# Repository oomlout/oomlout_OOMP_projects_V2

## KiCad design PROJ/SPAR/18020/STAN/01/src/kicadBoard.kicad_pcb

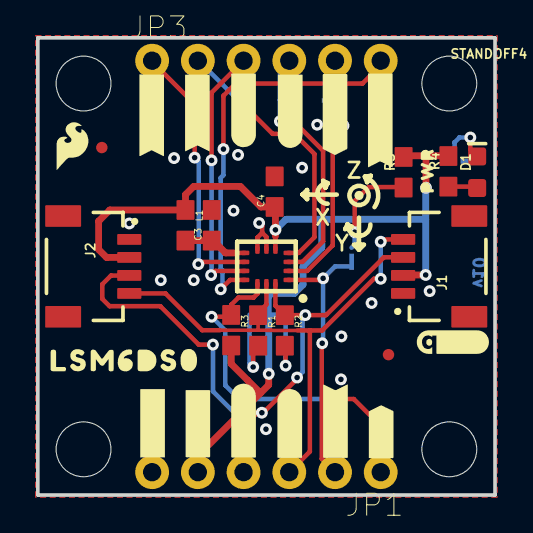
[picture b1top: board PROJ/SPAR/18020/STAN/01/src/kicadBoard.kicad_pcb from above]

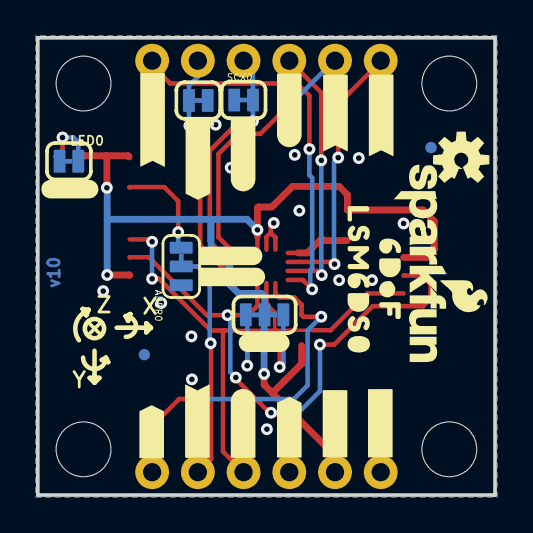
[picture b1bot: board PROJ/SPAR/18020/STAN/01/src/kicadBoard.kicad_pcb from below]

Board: 2 copper layers, 25.4 x 25.4 mm, 64 parts (27 on the bottom side), 18 nets.

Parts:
ADDR0: JUMPER-SMT_3_1-NC_TRACE_SILK; SMT-JUMPER_3_1-NC_TRACE_SILK
C3, C4: 0.1uF; 0603
D1: RED; LED-0603
FD1, FD2: FIDUCIALUFIDUCIAL; FIDUCIAL-MICRO
FID1, FID2: FIDUCIALUFIDUCIAL; FIDUCIAL-MICRO
FRAME1: FRAME-LETTER; CREATIVE_COMMONS
I2C_PU0: S_MODE; SMT-JUMPER_3_2-NC_TRACE_SILK
J1, J2: QWIIC_RIGHT_ANGLE; JST04_1MM_RA
JP1, JP3: IO; 1X06_NO_SILK
L1: 30Ω; 0603
LED0: JUMPER-SMT_2_NC_TRACE_SILK; SMT-JUMPER_2_NC_TRACE_SILK
LOGO1: QWIIC_LOGO_4MM; QWIIC_4MM
LOGO2: OSHW-LOGOS; OSHW-LOGO-S
LOGO3: SFE_LOGO_NAME_FLAME.1_INCH; SFE_LOGO_NAME_FLAME_.1
R1, R2: 4.7k; 0603
R3: 10k; 0603
R4: 1k; 0603
R5: 100k; 0603
SCX0: JUMPER-SMT_2_NC_TRACE_SILK; SMT-JUMPER_2_NC_TRACE_SILK
SDX0: JUMPER-SMT_2_NC_TRACE_SILK; SMT-JUMPER_2_NC_TRACE_SILK
STANDOFF1, STANDOFF2, STANDOFF3, STANDOFF4: STAND-OFFTIGHT; STAND-OFF-TIGHT
U1: LSM6DS0; LGA14L
U$1, U$15: #3V3#1
U$2, U$17: #GND#0
U$3: ##CS##7
U$4: #SDA#4
U$5, U$22: #SCL#5
U$6: #SDO#6
U$7, U$19: #INT1#9
U$8, U$21: #INT2#9
U$9: #OCS#8
U$10: #SCX#9
U$11, U$33: #SDIX#11
U$12, U$30: LSM6DS011
U$13: #0X6A#11
U$14: #0X6B#11
U$16: #LED#11
U$18: #SDO#7
U$20: #OCS#7
U$23: #SCX#8
U$24, U$32: #SDOX#12
U$25: #I2C#11
U$26: #SDI#4
U$27: ##CS##8
U$28: PWR8
U$29: SFE_LOGO_FLAME_.1
U$31: 6DOF12

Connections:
3.3V: C4.1, I2C_PU0.2, J1.2, J2.2, JP1.5, L1.1, R3.2, R4.2, R5.2, U1.5
GND: ADDR0.1, C3.2, C4.2, J1.1, J2.1, JP1.6, LED0.1, SCX0.1, SDX0.1, U1.6, U1.7
INT1: JP3.2, U1.4
INT2: JP3.1, U1.9
unnamed: ADDR0.3, R5.1
unnamed: D1.A, R4.1
unnamed: D1.C, LED0.2
unnamed: I2C_PU0.1, R1.2
unnamed: I2C_PU0.3, R2.2
OCS: JP3.3, U1.10
SCL: J1.4, J2.4, JP1.3, R1.1, U1.13
SCX: JP3.4, SCX0.2, U1.3
SDA: J1.3, J2.3, JP1.4, R2.1, U1.14
SDI_AUX: JP3.5, SDX0.2, U1.2
SDO/SA0: ADDR0.2, JP1.2, U1.1
SDO_AUX: JP3.6, U1.11
VDD: C3.1, L1.2, U1.8
~CS: JP1.1, R3.1, U1.12

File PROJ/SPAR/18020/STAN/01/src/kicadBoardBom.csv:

"Id";"Designator";"Package";"Quantity";"Designation";"Supplier and ref";
1;"U$30,U$12";"LSM6DS011";2;"";;;
2;"C3,C4";"0603";2;"0.1uF";;;
3;"STANDOFF4,STANDOFF3,STANDOFF2,STANDOFF1";"STAND-OFF-TIGHT";4;"STAND-OFFTIGHT";;;
4;"J1,J2";"JST04_1MM_RA";2;"QWIIC_RIGHT_ANGLE";;;
5;"L1";"0603";1;"30Ω";;;
6;"FID1,FID2,FD2,FD1";"FIDUCIAL-MICRO";4;"FIDUCIALUFIDUCIAL";;;
7;"LOGO1";"QWIIC_4MM";1;"QWIIC_LOGO_4MM";;;
8;"U$28";"PWR8";1;"";;;
9;"U$6";"#SDO#6";1;"";;;
10;"R3";"0603";1;"10k";;;
11;"U$2,U$17";"#GND#0";2;"";;;
12;"R1,R2";"0603";2;"4.7k";;;
13;"JP1,JP3";"1X06_NO_SILK";2;"IO";;;
14;"U$3";"##CS##7";1;"";;;
15;"R4";"0603";1;"1k";;;
16;"U$4";"#SDA#4";1;"";;;
17;"R5";"0603";1;"100k";;;
18;"U$8,U$21";"#INT2#9";2;"";;;
19;"FRAME1";"CREATIVE_COMMONS";1;"FRAME-LETTER";;;
20;"U$1,U$15";"#3V3#1";2;"";;;
21;"U$5,U$22";"#SCL#5";2;"";;;
22;"U$11,U$33";"#SDIX#11";2;"";;;
23;"U$24,U$32";"#SDOX#12";2;"";;;
24;"U$10";"#SCX#9";1;"";;;
25;"U$9";"#OCS#8";1;"";;;
26;"U$7,U$19";"#INT1#9";2;"";;;
27;"U1";"LGA14L";1;"LSM6DS0";;;
28;"U$29";"SFE_LOGO_FLAME_.1";1;"";;;
29;"D1";"LED-0603";1;"RED";;;
30;"U$31";"6DOF12";1;"";;;
31;"U$14";"#0X6B#11";1;"";;;
32;"ADDR0";"SMT-JUMPER_3_1-NC_TRACE_SILK";1;"JUMPER-SMT_3_1-NC_TRACE_SILK";;;
33;"I2C_PU0";"SMT-JUMPER_3_2-NC_TRACE_SILK";1;"S_MODE";;;
34;"U$25";"#I2C#11";1;"";;;
35;"LOGO3";"SFE_LOGO_NAME_FLAME_.1";1;"SFE_LOGO_NAME_FLAME.1_INCH";;;
36;"U$16";"#LED#11";1;"";;;
37;"SCX0,SDX0,LED0";"SMT-JUMPER_2_NC_TRACE_SILK";3;"JUMPER-SMT_2_NC_TRACE_SILK";;;
38;"U$18";"#SDO#7";1;"";;;
39;"U$26";"#SDI#4";1;"";;;
40;"LOGO2";"OSHW-LOGO-S";1;"OSHW-LOGOS";;;
41;"U$23";"#SCX#8";1;"";;;
42;"U$13";"#0X6A#11";1;"";;;
43;"U$20";"#OCS#7";1;"";;;
44;"U$27";"##CS##8";1;"";;;

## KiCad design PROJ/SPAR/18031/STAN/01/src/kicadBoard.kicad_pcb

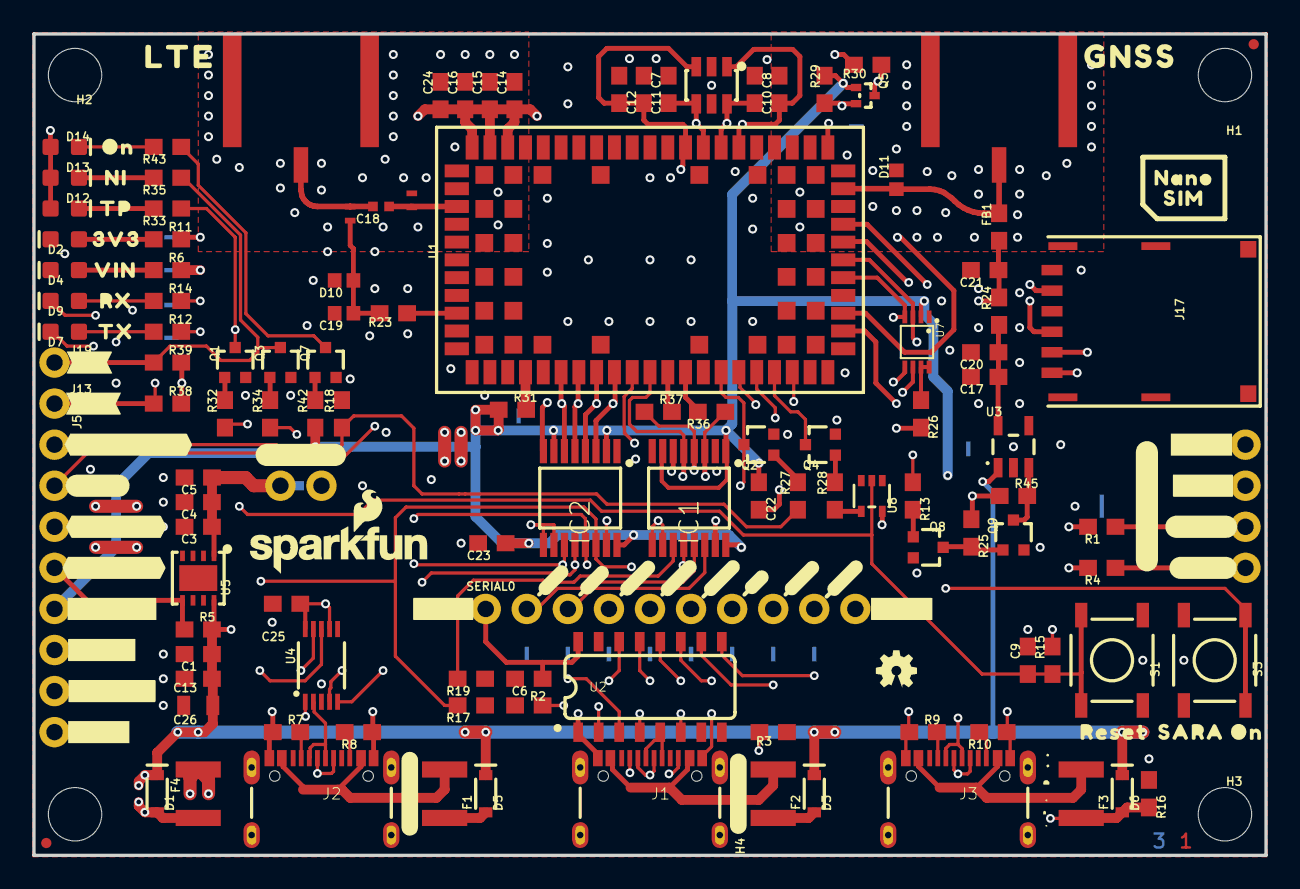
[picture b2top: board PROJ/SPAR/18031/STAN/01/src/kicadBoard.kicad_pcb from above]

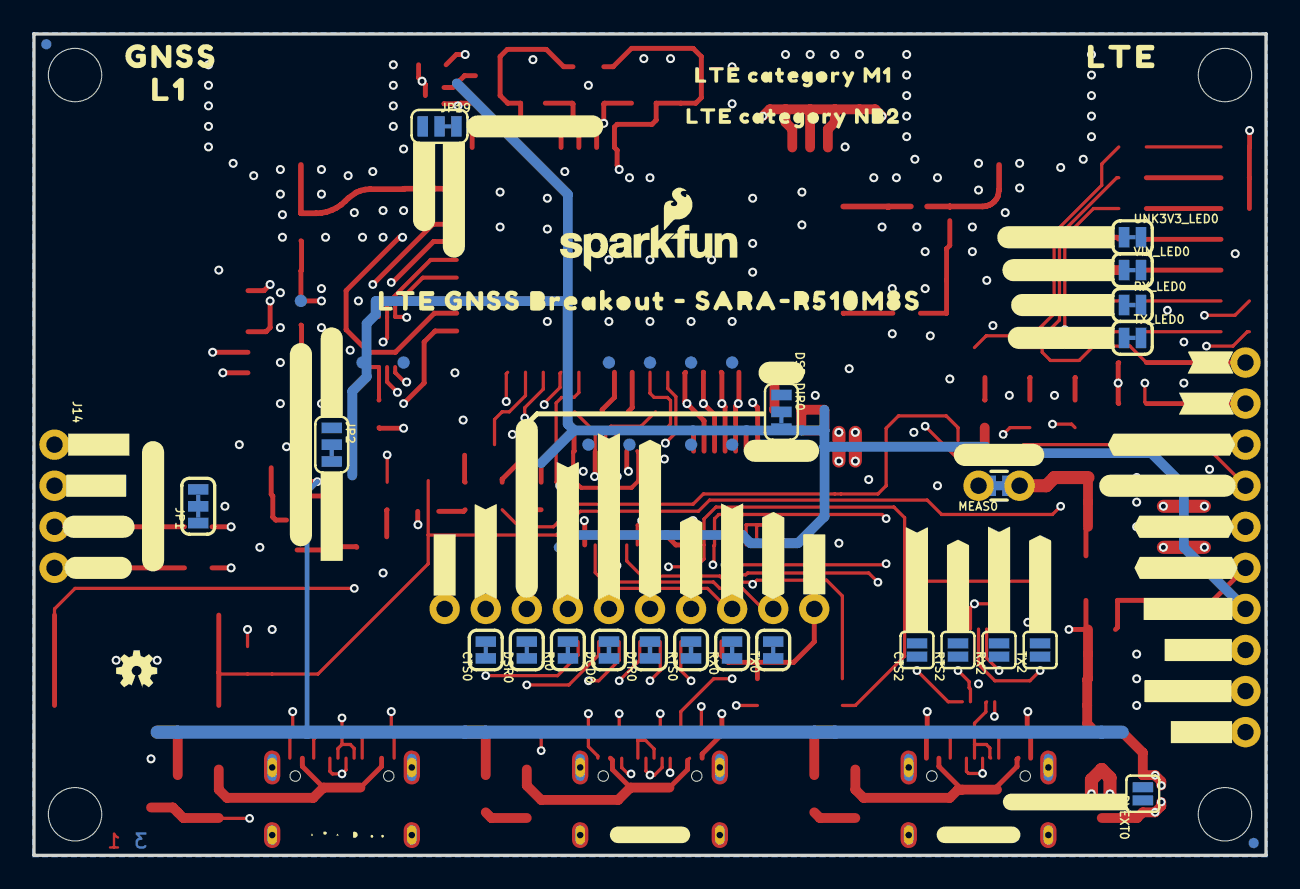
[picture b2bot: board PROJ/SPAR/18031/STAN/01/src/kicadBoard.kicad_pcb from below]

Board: 4 copper layers, 76.2 x 50.8 mm, 256 parts (90 on the bottom side), 111 nets.

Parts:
C1, C4, C6, C9, C12, C14, C20, C22, C23, C25: 0.1uF; 0603
C3: 4.7uF; 0603
C5, C13: 0.22uF; 0603
C7, C8, C10, C11, C21: 47pF; 0603
C15: 68pF; 0603
C16: 10uF; 0603
C17: 1.0uF; 0603
C18: 33pF; 0402-TIGHT
C19: 27pF; 0402
C24: 15pF; 0603
C26: 10uF; 0805
CTS0: JUMPER-SMT_2_NC_TRACE_SILK; SMT-JUMPER_2_NC_TRACE_SILK
CTS2: JUMPER-SMT_2_NO_SILK; SMT-JUMPER_2_NO_SILK
D1, D3, D5, D6: 3A/10V/280mV; SOD-323
D2: RED; LED-0603
D4, D9: Yellow; LED-0603
D7, D12: GREEN; LED-0603
D8: DT1042-04SO-7; SOT23-6L
D10, D11: PESD0402; 0402
D13: BLUE; LED-0603
D14: WHITE; LED-0603
DCD0: JUMPER-SMT_2_NC_TRACE_SILK; SMT-JUMPER_2_NC_TRACE_SILK
DSR0: JUMPER-SMT_2_NC_TRACE_SILK; SMT-JUMPER_2_NC_TRACE_SILK
DSR_DIR0: JUMPER-SMT_3_1-NC_TRACE_SILK; SMT-JUMPER_3_1-NC_TRACE_SILK
DTR0: JUMPER-SMT_2_NC_TRACE_SILK; SMT-JUMPER_2_NC_TRACE_SILK
DVEXT0: JUMPER-SMT_2_NO_SILK; SMT-JUMPER_2_NO_SILK
E3, E4: ANTENNA-SMA-GROUNDEDEDGE_SMA_SMD; SMA-EDGE-SMD
F1, F2, F3, F4: 6V/2A; 1210
FB1: 30Ω/1.8A; 0603
FD1, FD2, FD3, FD4: FIDUCIALUFIDUCIAL; FIDUCIAL-MICRO
FRAME1: FRAME-LEDGER; CREATIVE_COMMONS
H1, H2, H3, H4: STAND-OFF
IC1, IC2: SN74AVC4T774PW; SOP65P640X120-16N
J1, J2, J3: USB-C-16P_4LAYER-PADS
J5: 1X08_NO_SILK
J13: TP; 1X01_NO_SILK
J14: 1X04_NO_SILK
J17: NANO_SIM; NANO_SIM_WURTH_693043020611
J19: NI; 1X01_NO_SILK
JP1: SMT-JUMPER_3_2-NC_TRACE_SILK
JP2, JP19: JUMPER-SMT_3_1-NC_TRACE_SILK; SMT-JUMPER_3_1-NC_TRACE_SILK
L1: DNP; 0402_COILCRAFT
L2: 68nH; 0402_COILCRAFT
LOGO1, LOGO4: SFE_LOGO_NAME_FLAME.1_INCH; SFE_LOGO_NAME_FLAME_.1
LOGO2, LOGO3: OSHW-LOGOMINI; OSHW-LOGO-MINI
LOGO5: SPECIAL_INSTRUCTIONS-ORDERING; ORDERING_INSTRUCTIONS
MEAS0: COMBO-JUMPER_2_NC_TRACE
Q1, Q2, Q3, Q4, Q7, Q8, Q9: 310mA/60V/1.6Ω; SOT323
Q5: 20V/0.2A/8MHz/1.2Ω/1Vth; SOT-416FL
R1, R4, R29, R30: 2.2k; 0603
R2, R3, R7, R8, R9, R10, R16: 5.1k; 0603
R5, R15, R17, R18, R19, R25, R38, R39, R45: 100k; 0603
R6, R12, R14: 4.7k; 0603
R11, R13, R27, R28, R32, R34, R42, R43: 1k; 0603
R23: 10k; 0603
R24: 10; 0603
R26: 200k; 0603
R31, R36, R37: 0; 0603
R33: 100; 0603
R35: 470; 0603
RI0: JUMPER-SMT_2_NC_TRACE_SILK; SMT-JUMPER_2_NC_TRACE_SILK
RTS0: JUMPER-SMT_2_NC_TRACE_SILK; SMT-JUMPER_2_NC_TRACE_SILK
RTS2: JUMPER-SMT_2_NO_SILK; SMT-JUMPER_2_NO_SILK
RX0: JUMPER-SMT_2_NC_TRACE_SILK; SMT-JUMPER_2_NC_TRACE_SILK
RX2: JUMPER-SMT_2_NO_SILK; SMT-JUMPER_2_NO_SILK
RX_LED0: SMT-JUMPER_2_NC_TRACE_SILK
S1: RESET; TACTILE_SWITCH_SMD_5.2MM
S3: SARA_PWR; TACTILE_SWITCH_SMD_5.2MM
SERIAL0: 1X10_NO_SILK
TP1, TP2, TP3, TP4, TP9, TP10, TP14, TP15, TP16, TP17, TP22: TEST-POINT3; PAD.03X.03
TX0: JUMPER-SMT_2_NC_TRACE_SILK; SMT-JUMPER_2_NC_TRACE_SILK
TX2: JUMPER-SMT_2_NO_SILK; SMT-JUMPER_2_NO_SILK
TX_LED0: SMT-JUMPER_2_NC_TRACE_SILK
U1: SARA-R510M8S; SARA-LGA
U2: CH340C; SO016
U3: 3.3V; SOT23-5
U4: CH340E_MSOP10; MSOP10
U5: AP7361C-33FGE; UDFN-8
U7: PCA9306; VSSOP_8PIN
U8: 74HC1G04; SOT353
U$1, U$2, U$3, U$11: #3V3#1
U$4: #TX_LED#0
U$5, U$23: #SARA_I�C#0
U$6, U$7: #V_EXT#0
U$8, U$9: #3V3EN#0
U$10, U$13: ##RESET##0
U$12, U$22: #GND#0
U$14: #INT#0
U$15, U$71: #SARA_INT#0
U$16, U$17: #SARA_ON#0
U$18: RX0
U$19, U$87: #MEAS#2
U$20: #RX_LED#0
U$21: TX0
U$24: #TX#0
U$25: #RX#0
U$26, U$27: #SCL#3
U$28: #RTS#0
U$29: #DTR#0
U$30, U$37: #SDA#2
U$31: #DCD#0
U$32: #RI#0
U$33: #DSR#0
U$34: #CTS#0
U$35: #RXD_O#0
U$36: 3V37
U$38: #TXD_I#0
U$39: #CTS_O#0
U$40: #RTS_I#0
U$41: #DTR_TXD2_I#0
U$42: L10
U$43: #DCD_RXD2_O#0
U$44: #RXD2_O#0
U$45: RESET6
U$46: VIN8
U$47: #RI_CTS2_O#0
U$48: #CTS2_O#0
U$49: #DSR_O__RTS2_I#0
U$50: #RTS2_I#0
U$51: #V_EXT_DIODE#0
U$52: #OUT#0
U$53: #IN#0
U$54: #VIN_LED#0
U$55, U$56, U$81, U$82: #GND#4
U$57, U$58: #TP#0
U$59, U$60: #NI#0
U$61: #3V3_LED#0
U$62, U$63: #UART_2#0
U$64, U$65: #UART_1#0
U$66, U$67: #SARA_DIAG#0
U$68, U$80, U$83: #VCCIO#0
U$69: #GPIO2#0
U$70: #ANT_GNSS_PWR#0
U$72: #TXD2_I#0
U$73: LTE_CATEGORY_M10
U$74: LTE_CATEGORY_NB20
U$75: LTE_GNSS_BREAKOUT_#_SARA#R510M8S0
U$76, U$79: #3#3V#0
U$88, U$89: LTE0
U$90: NI0
U$91: TP0
U$99, U$100: GNSS0
U$101: ON0
U$113: SARA_ON0
U$118: #EXT_INT#0
U$119: #GPIO3#0
U$130: NANO0
U$131: SIM0
UNK3V3_LED0: SMT-JUMPER_2_NC_TRACE_SILK
VIN_LED0: SMT-JUMPER_2_NC_TRACE_SILK

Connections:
3.3V: C6.1, C14.1, C15.1, C16.1, C24.1, C25.1, D12.A, D13.A, D14.A, IC1.15, IC2.15, J5.6, J14.2, JP1.2, MEAS0.2, MEAS0.4, R15.2, R25.1, R26.2, R30.2, R38.2, R39.2, R45.1, RX_LED0.2, SERIAL0.1, TX_LED0.2, U1.51, U1.52, U1.53, U2.4, U2.16, U4.7, U4.10, U8.5, UNK3V3_LED0.2
3.3V_EN: J5.4, R5.1, U5.5
ANT_REG_EN: Q9.3, R45.2, U3.3
CTS: CTS0.2, IC1.12, SERIAL0.9
DCD: DCD0.2, IC2.13, RX2.2, SERIAL0.6
DSR: DSR0.2, IC2.11, RTS2.2, SERIAL0.8
DTR: DTR0.2, IC2.14, R17.2, SERIAL0.5, TX2.2
GND: C1.2, C3.2, C4.2, C5.2, C6.2, C7.2, C8.2, C9.2, C10.1, C11.1, C12.1, C13.2, C14.2, C15.2, C16.2, C17.2, C19.2, C20.2, C21.2, C22.2, C23.2, C24.2, C25.2, C26.2, D2.C, D4.C, D8.2, D8.5, D10.2, D11.2, DSR_DIR0.1, E3.GND@0, E3.GND@1, E4.GND@0, E4.GND@1, IC1.2, IC1.8, IC1.9, IC1.10, IC2.1, IC2.9, IC2.10, J1.GND, J1.GND2, J2.GND, J2.GND2, J3.GND, J3.GND2, J5.8, J14.1, J17.C5, L1.P$2, Q1.2, Q2.2, Q3.2, Q4.2, Q7.2, Q8.2, Q9.2, R2.1, R3.1, R7.1, R8.1, R9.1, R10.1, R16.1, R17.1, R18.2, R19.1, S1.1, S1.2, S3.3, S3.4, SERIAL0.10, U1.1, U1.3, U1.5, U1.14, U1.20, U1.21, U1.22, U1.30, U1.32, U1.43, U1.50, U1.54, U1.55, U1.57, U1.58, U1.59, U1.60, U1.61, U1.63, U1.64, U1.65, U1.66, U1.67, U1.68, U1.69, U1.70, U1.71, U1.72, U1.73, U1.74, U1.75, U1.76, U1.77, U1.78, U1.79, U1.80, U1.81, U1.82, U1.83, U1.84, U1.85, U1.86, U1.87, U1.88, U1.89, U1.90, U1.91, U1.92, U1.93, U1.94, U1.95, U1.96, U2.1, U3.2, U4.3, U5.4, U5.EP, U7.P1, U8.3
unnamed: R6.2, VIN_LED0.1
unnamed: JP1.3, R4.2
unnamed: JP1.1, R1.2
unnamed: D3.A, F2.2
unnamed: J2.A5, R7.2
unnamed: R11.2, UNK3V3_LED0.1
unnamed: D2.A, R11.1
unnamed: D4.A, R6.1
unnamed: J2.B5, R8.2
unnamed: J1.A5, R2.2
unnamed: J1.B5, R3.2
unnamed: D5.A, F1.2
unnamed: F1.1, J2.VBUS1, J2.VBUS2
unnamed: J3.A5, R9.2
unnamed: C18.2, E3.SIG, L2.P$2
unnamed: C19.1, D10.1, L2.P$1, R23.2
unnamed: J3.B5, R10.2
unnamed: F3.1, J3.VBUS1, J3.VBUS2
unnamed: F2.1, J1.VBUS1, J1.VBUS2
unnamed: TX0.1, U2.2
unnamed: RX0.1, U2.3
unnamed: R26.1, U7.P7, U7.P8
unnamed: DSR_DIR0.2, IC2.8
unnamed: C17.1, C20.1, R24.1, U3.5
unnamed: C21.1, FB1.1, R24.2, TP22.P$1
unnamed: Q2.1, R27.2
unnamed: Q4.1, R28.2
unnamed: R28.1, U8.4
unnamed: RTS0.1, U2.14
unnamed: DTR0.1, U2.13
unnamed: R31.2, U1.4
unnamed: Q1.1, R32.2
unnamed: J13.1, Q1.3, R33.1, R38.1
unnamed: D12.C, R33.2
unnamed: Q3.1, R34.2
unnamed: J19.1, Q3.3, R35.1, R39.1
unnamed: D13.C, R35.2
unnamed: R36.2, U1.13
unnamed: R37.2, U1.12
unnamed: Q8.1, R13.2
unnamed: DCD0.1, U2.12
unnamed: Q8.3, Q9.1, R25.2
unnamed: JP19.2, Q5.2, R29.1
unnamed: RI0.1, U2.11
unnamed: DSR0.1, U2.10
unnamed: CTS0.1, U2.9
unnamed: Q7.1, R42.2
unnamed: TX2.1, U4.8
unnamed: D14.C, R43.2
unnamed: RX2.1, U4.9
unnamed: RTS2.1, U4.4
unnamed: CTS2.1, U4.5
unnamed: R12.2, TX_LED0.1
unnamed: D7.A, R12.1
unnamed: R14.2, RX_LED0.1
unnamed: D9.A, R14.1
unnamed: D1.A, DVEXT0.1, F4.1
unnamed: JP2.2, R13.1
RI: CTS2.2, IC2.12, RI0.2, SERIAL0.7
RTS: IC1.11, R19.2, RTS0.2, SERIAL0.4
RX: D9.C, IC1.14, RX0.2, SERIAL0.3
SARA_ANT: C18.1, L1.P$1, U1.56
SARA_ANT_DET: R23.1, U1.62
SARA_ANT_GNSS: D11.1, E4.SIG, FB1.2, U1.31
SARA_CTS_O: IC1.5, TP3.P$1, U1.11
SARA_DCD/RXD2O: IC2.4, TP15.P$1, U1.8
SARA_DSR/RTS2I: IC2.6, TP17.P$1, U1.6
SARA_DTR/TXD2I: IC2.3, TP14.P$1, U1.9
SARA_EXT_INT: JP19.3, U1.33
SARA_GPIO2: JP2.1, U1.23
SARA_GPIO3: JP19.1, U1.24
SARA_INT: J5.2, Q5.3, R30.1
SARA_NI: R34.1, U1.16
SARA_ON: J5.1, R18.1, R27.1
SARA_ON_1.8V: Q2.3, S3.1, S3.2, U1.15
SARA_RI/CTS2O: IC2.5, TP16.P$1, U1.7
SARA_RTS_I: IC1.6, TP4.P$1, U1.10
SARA_RXD_O: IC1.3, R36.1, TP1.P$1
SARA_SCL: J14.4, R4.1, U7.P6
SARA_SCL_1.8V: TP10.P$1, U1.27, U7.P3
SARA_SDA: J14.3, R1.1, U7.P5
SARA_SDA_1.8V: TP9.P$1, U1.26, U7.P4
SARA_TP: R32.1, U1.19
SARA_TXD_I: IC1.4, R37.1, TP2.P$1
SARA_USB_D+: J3.A6, J3.B6, U1.29
SARA_USB_D-: J3.A7, J3.B7, U1.28
SARA_VUSB_DET: D6.A, F3.2, R16.2, U1.17
SARA_~ON: Q7.3, R43.1
SARA_~RESET: Q4.3, U1.18
SIM_CLK: C8.1, D8.1, J17.C3, U1.38
SIM_IO: C10.2, D8.6, J17.C7, U1.39
SIM_RST: C7.1, D8.4, J17.C2, U1.40
TX: D7.C, IC1.13, SERIAL0.2, TX0.2
USB_2_D+: J2.A6, J2.B6, U4.1
USB_2_D-: J2.A7, J2.B7, U4.2
USB_D+: J1.A6, J1.B6, U2.5
USB_D-: J1.A7, J1.B7, U2.6
VCCIO: C22.1, C23.1, DSR_DIR0.3, IC1.1, IC1.7, IC1.16, IC2.2, IC2.7, IC2.16, J5.5, JP2.3, Q5.1, R29.2, R31.1, R42.1, U7.P2
VIN: C1.1, C13.1, C26.1, D1.C, D3.C, D5.C, D6.C, DVEXT0.2, R5.2, U3.1, U5.8, VIN_LED0.2
VREG_3.3V: C3.1, C4.1, C5.1, MEAS0.1, MEAS0.3, U5.1
VSIM: C11.2, C12.2, D8.3, J17.C1, U1.41
V_EXT: F4.2, J5.7
~RESET: C9.1, J5.3, R15.1, S1.3, S1.4, U8.2

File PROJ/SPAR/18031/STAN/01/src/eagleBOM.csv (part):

"Part";"Value";"Device";"Package";"Description";"DESIGNER";"DIGIKEY_PART";"MOUSER_PART";"MOUSE_PART";"PROD_ID";"REV";"VALUE";
"3V3_LED";"";"JUMPER-SMT_2_NC_TRACE_SILK";"SMT-JUMPER_2_NC_TRACE_SILK";"Normally closed trace jumper";"";"";"";"";"";"";"";
"C1";"0.1uF";"0.1UF-0603-25V-5%";"0603";"0.1µF ceramic capacitors";"";"";"";"";"CAP-08604";"";"0.1uF";
"C3";"4.7uF";"4.7UF-0603-6.3V-(10%)";"0603";"4.7µF ceramic capacitors";"";"";"";"";"CAP-08280";"";"4.7uF";
"C4";"0.1uF";"0.1UF-0603-25V-5%";"0603";"0.1µF ceramic capacitors";"";"";"";"";"CAP-08604";"";"0.1uF";
"C5";"0.22uF";"0.22UF-0603-25V-10%";"0603";"0.22µF ceramic capacitors";"";"";"";"";"CAP-07822";"";"0.22uF";
"C6";"0.1uF";"0.1UF-0603-25V-5%";"0603";"0.1µF ceramic capacitors";"";"";"";"";"CAP-08604";"";"0.1uF";
"C7";"47pF";"47PF-0603-50V-5%";"0603";"47pF ceramic capacitors";"";"";"";"";"CAP-08913";"";"47pF";
"C8";"47pF";"47PF-0603-50V-5%";"0603";"47pF ceramic capacitors";"";"";"";"";"CAP-08913";"";"47pF";
"C9";"0.1uF";"0.1UF-0603-25V-5%";"0603";"0.1µF ceramic capacitors";"";"";"";"";"CAP-08604";"";"0.1uF";
"C10";"47pF";"47PF-0603-50V-5%";"0603";"47pF ceramic capacitors";"";"";"";"";"CAP-08913";"";"47pF";
"C11";"47pF";"47PF-0603-50V-5%";"0603";"47pF ceramic capacitors";"";"";"";"";"CAP-08913";"";"47pF";
"C12";"0.1uF";"0.1UF-0603-25V-5%";"0603";"0.1µF ceramic capacitors";"";"";"";"";"CAP-08604";"";"0.1uF";
"C13";"0.22uF";"0.22UF-0603-25V-10%";"0603";"0.22µF ceramic capacitors";"";"";"";"";"CAP-07822";"";"0.22uF";
"C14";"0.1uF";"0.1UF-0603-25V-5%";"0603";"0.1µF ceramic capacitors";"";"";"";"";"CAP-08604";"";"0.1uF";
"C15";"68pF";"68PF-0603-50V-5%";"0603";"68pF ceramic capacitors";"";"";"";"";"CAP-14092";"";"68pF";
"C16";"10uF";"10UF-0603-6.3V-20%";"0603";"10.0µF ceramic capacitors";"";"";"";"";"CAP-11015";"";"10uF";
"C17";"1.0uF";"1.0UF-0603-16V-10%";"0603";"1µF ceramic capacitors";"";"";"";"";"CAP-00868";"";"1.0uF";
"C18";"33pF";"33PF-0402T-50V-5%";"0402-TIGHT";"33pF ceramic capacitors";"";"";"";"";"CAP-15358";"";"33pF";
"C19";"27pF";"27PF-0402-50V-5%";"0402";"27pF ceramic capacitors";"";"";"";"";"CAP-15357";"";"27pF";
"C20";"0.1uF";"0.1UF-0603-25V-5%";"0603";"0.1µF ceramic capacitors";"";"";"";"";"CAP-08604";"";"0.1uF";
"C21";"47pF";"47PF-0603-50V-5%";"0603";"47pF ceramic capacitors";"";"";"";"";"CAP-08913";"";"47pF";
"C22";"0.1uF";"0.1UF-0603-25V-5%";"0603";"0.1µF ceramic capacitors";"";"";"";"";"CAP-08604";"";"0.1uF";
"C23";"0.1uF";"0.1UF-0603-25V-5%";"0603";"0.1µF ceramic capacitors";"";"";"";"";"CAP-08604";"";"0.1uF";
"C24";"15pF";"15PF-0603-50V-5%";"0603";"15pF ceramic capacitors";"";"";"";"";"CAP-07881";"";"15pF";
"C25";"0.1uF";"0.1UF-0603-25V-5%";"0603";"0.1µF ceramic capacitors";"";"";"";"";"CAP-08604";"";"0.1uF";
"C26";"10uF";"10UF-0805-25V-10%";"0805";"10.0µF ceramic capacitors";"";"";"";"";"CAP-14259";"";"10uF";
"CTS";"JUMPER-SMT_2_NC_TRACE_SILK";"JUMPER-SMT_2_NC_TRACE_SILK";"SMT-JUMPER_2_NC_TRACE_SILK";"Normally closed trace jumper";"";"";"";"";"";"";"";
"CTS2";"JUMPER-SMT_2_NO_SILK";"JUMPER-SMT_2_NO_SILK";"SMT-JUMPER_2_NO_SILK";"Normally open jumper";"";"";"";"";"";"";"";
"D1";"3A/10V/280mV";"DIODE-SCHOTTKY-BAT60A";"SOD-323";"Schottky diode";"";"";"";"";"DIO-14072";"";"3A/10V/280mV";
"D2";"RED";"LED-RED0603";"LED-0603";"Red SMD LED";"";"";"";"";"DIO-00819";"";"RED";
"D3";"3A/10V/280mV";"DIODE-SCHOTTKY-BAT60A";"SOD-323";"Schottky diode";"";"";"";"";"DIO-14072";"";"3A/10V/280mV";
"D4";"Yellow";"LED-YELLOW0603";"LED-0603";"Yellow SMD LED";"";"";"";"";"DIO-09003";"";"Yellow";
"D5";"3A/10V/280mV";"DIODE-SCHOTTKY-BAT60A";"SOD-323";"Schottky diode";"";"";"";"";"DIO-14072";"";"3A/10V/280mV";
"D6";"3A/10V/280mV";"DIODE-SCHOTTKY-BAT60A";"SOD-323";"Schottky diode";"";"";"";"";"DIO-14072";"";"3A/10V/280mV";
"D7";"GREEN";"LED-GREEN0603";"LED-0603";"Green SMD LED";"";"";"";"";"DIO-00821";"";"GREEN";
"D8";"DT1042-04SO-7";"TVS_DIODE_ARRAY_4DT1042-04SO-7";"SOT23-6L";"";"";"";"";"";"DIO-14095";"";"";
"D9";"Yellow";"LED-YELLOW0603";"LED-0603";"Yellow SMD LED";"";"";"";"";"DIO-09003";"";"Yellow";
"D10";"PESD0402";"PESD0402";"0402";"ESD protection diode";"";"PESD0402-140CT-ND";"";"650-PESD0402-140";"DIO-15359";"";"";
"D11";"PESD0402";"PESD0402";"0402";"ESD protection diode";"";"PESD0402-140CT-ND";"";"650-PESD0402-140";"DIO-15359";"";"";
"D12";"GREEN";"LED-GREEN0603";"LED-0603";"Green SMD LED";"";"";"";"";"DIO-00821";"";"GREEN";
"D13";"BLUE";"LED-BLUE0603";"LED-0603";"Blue SMD LED";"";"";"";"";"DIO-08575";"";"BLUE";
"D14";"WHITE";"LED-WHITE0603";"LED-0603";"White SMD LED";"";"";"";"";"DIO-09004";"";"WHITE";
"DCD";"JUMPER-SMT_2_NC_TRACE_SILK";"JUMPER-SMT_2_NC_TRACE_SILK";"SMT-JUMPER_2_NC_TRACE_SILK";"Normally closed trace jumper";"";"";"";"";"";"";"";
"DSR";"JUMPER-SMT_2_NC_TRACE_SILK";"JUMPER-SMT_2_NC_TRACE_SILK";"SMT-JUMPER_2_NC_TRACE_SILK";"Normally closed trace jumper";"";"";"";"";"";"";"";
"DSR_DIR";"JUMPER-SMT_3_1-NC_TRACE_SILK";"JUMPER-SMT_3_1-NC_TRACE_SILK";"SMT-JUMPER_3_1-NC_TRACE_SILK";"Normally closed trace jumper (1 of 2 connections)";"";"";"";"";"";"";"";
"DTR";"JUMPER-SMT_2_NC_TRACE_SILK";"JUMPER-SMT_2_NC_TRACE_SILK";"SMT-JUMPER_2_NC_TRACE_SILK";"Normally closed trace jumper";"";"";"";"";"";"";"";
"DVEXT";"JUMPER-SMT_2_NO_SILK";"JUMPER-SMT_2_NO_SILK";"SMT-JUMPER_2_NO_SILK";"Normally open jumper";"";"";"";"";"";"";"";
"E3";"ANTENNA-SMA-GROUNDEDEDGE_SMA_SMD";"ANTENNA-SMA-GROUNDEDEDGE_SMA_SMD";"SMA-EDGE-SMD";"SMA Antenna Connector w/ Ground";"";"";"";"";"CONN-15100";"";"";
"E4";"ANTENNA-SMA-GROUNDEDEDGE_SMA_SMD";"ANTENNA-SMA-GROUNDEDEDGE_SMA_SMD";"SMA-EDGE-SMD";"SMA Antenna Connector w/ Ground";"";"";"";"";"CONN-15100";"";"";
"F1";"6V/2A";"PPTC_6V2A";"1210";"Resettable Fuse PPTC";"";"";"";"";"RES-14313";"";"6V/2A";
"F2";"6V/2A";"PPTC_6V2A";"1210";"Resettable Fuse PPTC";"";"";"";"";"RES-14313";"";"6V/2A";
"F3";"6V/2A";"PPTC_6V2A";"1210";"Resettable Fuse PPTC";"";"";"";"";"RES-14313";"";"6V/2A";
"F4";"6V/2A";"PPTC_6V2A";"1210";"Resettable Fuse PPTC";"";"";"";"";"RES-14313";"";"6V/2A";
"FB1";"30Ω/1.8A";"FERRITE_BEAD-0603";"0603";"Ferrite Bead (blocks, cores, rings, chokes, etc.)";"";"";"";"";"NDUC-13805";"";"30Ω/1.8A";
"FD1";"FIDUCIALUFIDUCIAL";"FIDUCIALUFIDUCIAL";"FIDUCIAL-MICRO";"Fiducial Alignment Points";"";"";"";"";"";"";"";
"FD2";"FIDUCIALUFIDUCIAL";"FIDUCIALUFIDUCIAL";"FIDUCIAL-MICRO";"Fiducial Alignment Points";"";"";"";"";"";"";"";
"FD3";"FIDUCIALUFIDUCIAL";"FIDUCIALUFIDUCIAL";"FIDUCIAL-MICRO";"Fiducial Alignment Points";"";"";"";"";"";"";"";
"FD4";"FIDUCIALUFIDUCIAL";"FIDUCIALUFIDUCIAL";"FIDUCIAL-MICRO";"Fiducial Alignment Points";"";"";"";"";"";"";"";
"FRAME1";"FRAME-LEDGER";"FRAME-LEDGER";"CREATIVE_COMMONS";"Schematic Frame - Ledger";"";"";"";"";"";"";"";
"H1";"STAND-OFF";"STAND-OFF";"STAND-OFF";"Stand Off";"";"";"";"";"";"";"";
"H2";"STAND-OFF";"STAND-OFF";"STAND-OFF";"Stand Off";"";"";"";"";"";"";"";
"H3";"STAND-OFF";"STAND-OFF";"STAND-OFF";"Stand Off";"";"";"";"";"";"";"";
"H4";"STAND-OFF";"STAND-OFF";"STAND-OFF";"Stand Off";"";"";"";"";"";"";"";
"IC1";"SN74AVC4T774PW";"SN74AVC4T774PW";"SOP65P640X120-16N";"Texas Instruments,SN74AVC4T774PW,IC, Texas Instruments SN74AVC4T774PW, Dual, Bus Transceiver, 4-Bit Non-Inverting 3-State, 1.2  3.6 V, 16-Pin TSSOP";"";"";"";"";"IC-15360";"";"SN74AVC4T774PW";
"IC2";"SN74AVC4T774PW";"SN74AVC4T774PW";"SOP65P640X120-16N";"Texas Instruments,SN74AVC4T774PW,IC, Texas Instruments SN74AVC4T774PW, Dual, Bus Transceiver, 4-Bit Non-Inverting 3-State, 1.2  3.6 V, 16-Pin TSSOP";"";"";"";"";"IC-15360";"";"SN74AVC4T774PW";
"J1";"";"USB_C_4-LAYER_PADS";"USB-C-16P_4LAYER-PADS";"USB Type C 16Pin Connector";"";"";"";"";"CONN-14122";"";"";
"J2";"";"USB_C_4-LAYER_PADS";"USB-C-16P_4LAYER-PADS";"USB Type C 16Pin Connector";"";"";"";"";"CONN-14122";"";"";
"J3";"";"USB_C_4-LAYER_PADS";"USB-C-16P_4LAYER-PADS";"USB Type C 16Pin Connector";"";"";"";"";"CONN-14122";"";"";
"J5";"";"CONN_08NO_SILK_DNP";"1X08_NO_SILK";"Multi connection point. Often used as Generic Header-pin footprint for 0.1 inch spaced/style header connections";"";"";"";"";"";"";"";
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
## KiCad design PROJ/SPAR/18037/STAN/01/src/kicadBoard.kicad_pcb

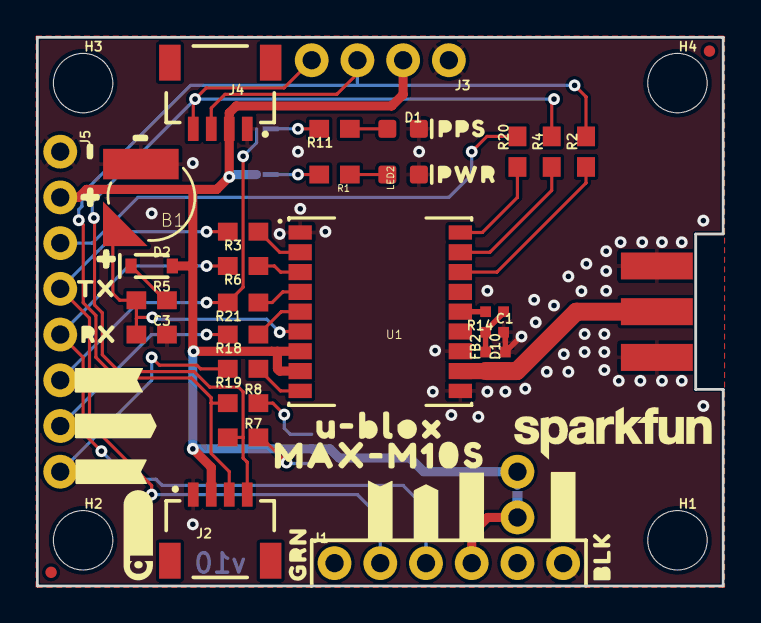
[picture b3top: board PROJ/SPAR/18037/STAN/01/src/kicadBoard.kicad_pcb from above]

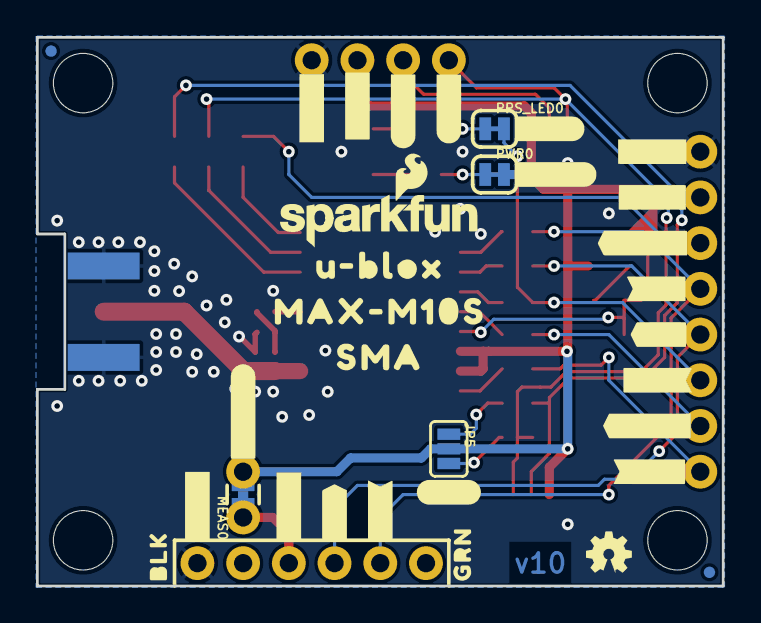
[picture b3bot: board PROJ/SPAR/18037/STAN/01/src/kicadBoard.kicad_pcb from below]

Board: 2 copper layers, 38.1 x 30.5 mm, 91 parts (33 on the bottom side), 30 nets.

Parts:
B1: 6.8MM_COIN_CELL; ML414H_IV01E
C1: 47pF; 0402-TIGHT
C3: 1.0uF; 0603
D1: Yellow; LED-0603
D2: 0.5A/40V/420mV; SOD-323
D10: PESD0402-0402T; 0402-TIGHT
E1: ANTENNA-SMA-GROUNDEDEDGE_SMA; SMA-EDGE
FB2: 2.66Ω; 0402-TIGHT
FD1, FD2, FD3, FD4: FIDUCIALUFIDUCIAL; FIDUCIAL-MICRO
FRAME1: FRAME-LETTER; CREATIVE_COMMONS
H1, H2, H3, H4: STAND-OFF
J1: USB-to-Serial; 1X06_NO_SILK
J2, J4: Qwiic Right Angle; JST04_1MM_RA
J3: PTH; 1X04_NO_SILK
J5: 1X08_NO_SILK
JP5: JUMPER-SMT_3_NO_SILK; SMT-JUMPER_3_NO_SILK
LED2: RED; LED-0603
LOGO1: OSHW-LOGOMINI; OSHW-LOGO-MINI
LOGO2: SFE_LOGO_NAME_FLAME.1_INCH; SFE_LOGO_NAME_FLAME_.1
LOGO3: QWIIC_LOGO_5MM; QWIIC_5MM
LOGO4: SFE_LOGO_NAME.1_INCH; SFE_LOGO_NAME_.1
MEAS0: JUMPER-COMBO_2_NC_TRACE; COMBO-JUMPER_2_NC_TRACE
PPS_LED0: JUMPER-SMT_2_NC_TRACE_SILK; SMT-JUMPER_2_NC_TRACE_SILK
PWR0: JUMPER-SMT_2_NC_TRACE_SILK; SMT-JUMPER_2_NC_TRACE_SILK
R1, R11: 1k; 0603
R2, R3, R4, R6, R18, R19, R20, R21: 33; 0603
R5: 3.3k; 0603
R7, R8: 2.2k; 0603
R14: 33OHM-0402T-1/10W-1%; 0402-TIGHT
U1: MAX-M10S
U$1, U$10, U$26, U$31: #3V3#4
U$2: SPECIAL_INSTRUCTIONS-ORDERING; ORDERING_INSTRUCTIONS
U$3, U$11, U$27, U$34: #GND#5
U$4, U$28: BLK0
U$5, U$29: GRN1
U$6: PPS7
U$7: PWR6
U$8, U$25: #RX#2
U$9, U$22: #TX#3
U$12: ##RST##2
U$13: ##SAFE##0
U$14, U$43: #PPS#1
U$15: #RX#1
U$16: #TX#0
U$18, U$23: MAX#M10S1
U$19, U$37: #0
U$20, U$21: U#BLOX0
U$24: SMA2
U$30: #I�C#0
U$32: #SCL#1
U$33: #SDA#0
U$35: #PPS#0
U$36: #PWR#0
U$38, U$40: #1
U$39: ##RST##0
U$41: #MEAS#0
U$42: #EINT#0
U$44: RX2
U$45: TX3
U$46: #EINT_#0

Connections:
3.3V: D2.A, J2.2, J3.2, J4.2, J5.2, JP5.2, MEAS0.2, MEAS0.4, PWR0.2, U1.7, U1.8
ANT_VCC: C1.1, FB2.2, R14.1
BACKUP: B1.+, C3.1, R5.1, U1.6
EXTINT_LV: R18.1, U1.5
GND: B1.-, C1.2, C3.2, D1.C, D10.2, E1.GND@0, E1.GND@1, E1.GND@2, E1.GND@3, J1.6, J2.1, J3.1, J4.1, J5.1, LED2.C, U1.1, U1.10, U1.12
GPS_RF: D10.1, E1.SIG, FB2.1, U1.11
INT: J5.7, R18.2
unnamed: J1.4, MEAS0.1, MEAS0.3
unnamed: D1.A, R11.1
unnamed: PPS_LED0.1, R11.2
unnamed: JP5.1, R8.2
unnamed: D2.C, R5.2
unnamed: JP5.3, R7.2
unnamed: LED2.A, R1.1
unnamed: PWR0.1, R1.2
PPS: J5.6, PPS_LED0.2, R21.2
PPS_LV: R21.1, U1.4
RST_LV: R19.1, U1.9
RXI: J1.3, J5.5, R6.2
RXLV: R6.1, U1.3
SAFE_LV: R20.1, U1.18
SCL: J2.4, J3.4, J4.4, R4.2, R7.1
SCL_LV: R4.1, U1.17
SDA: J2.3, J3.3, J4.3, R2.2, R8.1
SDA_LV: R2.1, U1.16
TXLV: R3.1, U1.2
TXO: J1.2, J5.4, R3.2
VCC_RF: R14.2, U1.14
~RESET: J5.8, R19.2
~SAFE: J5.3, R20.2

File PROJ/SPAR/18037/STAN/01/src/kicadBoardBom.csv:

"Id";"Designator";"Package";"Quantity";"Designation";"Supplier and ref";
1;"LED2";"LED-0603";1;"RED";;;
2;"R21,R4,R19,R20,R3,R18,R6,R2";"0603";8;"33";;;
3;"J5";"1X08_NO_SILK";1;"";;;
4;"U$18,U$23";"MAX#M10S1";2;"";;;
5;"C1";"0402-TIGHT";1;"47pF";;;
6;"U$20,U$21";"U#BLOX0";2;"";;;
7;"R1,R11";"0603";2;"1k";;;
8;"D10";"0402-TIGHT";1;"PESD0402-0402T";;;
9;"R7,R8";"0603";2;"2.2k";;;
10;"H1,H4,H2,H3";"STAND-OFF";4;"STAND-OFF";;;
11;"R14";"0402-TIGHT";1;"33OHM-0402T-1/10W-1%";;;
12;"J4,J2";"JST04_1MM_RA";2;"Qwiic Right Angle";;;
13;"U$5,U$29";"GRN1";2;"";;;
14;"U1";"MAX-M10S";1;"MAX-M10S";;;
15;"J3";"1X04_NO_SILK";1;"PTH";;;
16;"U$37,U$19";"#0";2;"";;;
17;"R5";"0603";1;"3.3k";;;
18;"U$39";"##RST##0";1;"";;;
19;"B1";"ML414H_IV01E";1;"6.8MM_COIN_CELL";;;
20;"E1";"SMA-EDGE";1;"ANTENNA-SMA-GROUNDEDEDGE_SMA";;;
21;"U$2";"ORDERING_INSTRUCTIONS";1;"SPECIAL_INSTRUCTIONS-ORDERING";;;
22;"D1";"LED-0603";1;"Yellow";;;
23;"FD3,FD1,FD4,FD2";"FIDUCIAL-MICRO";4;"FIDUCIALUFIDUCIAL";;;
24;"U$7";"PWR6";1;"";;;
25;"U$3,U$11,U$34,U$27";"#GND#5";4;"";;;
26;"U$9,U$22";"#TX#3";2;"";;;
27;"U$4,U$28";"BLK0";2;"";;;
28;"U$6";"PPS7";1;"";;;
29;"U$44";"RX2";1;"";;;
30;"FB2";"0402-TIGHT";1;"2.66Ω";;;
31;"U$45";"TX3";1;"";;;
32;"C3";"0603";1;"1.0uF";;;
33;"LOGO4";"SFE_LOGO_NAME_.1";1;"SFE_LOGO_NAME.1_INCH";;;
34;"J1";"1X06_NO_SILK";1;"USB-to-Serial";;;
35;"U$43,U$14";"#PPS#1";2;"";;;
36;"D2";"SOD-323";1;"0.5A/40V/420mV";;;
37;"LOGO3";"QWIIC_5MM";1;"QWIIC_LOGO_5MM";;;
38;"U$38,U$40";"#1";2;"";;;
39;"U$8,U$25";"#RX#2";2;"";;;
40;"U$1,U$26,U$31,U$10";"#3V3#4";4;"";;;
41;"FRAME1";"CREATIVE_COMMONS";1;"FRAME-LETTER";;;
42;"U$42";"#EINT#0";1;"";;;
43;"LOGO1";"OSHW-LOGO-MINI";1;"OSHW-LOGOMINI";;;
44;"U$35";"#PPS#0";1;"";;;
45;"U$41";"#MEAS#0";1;"";;;
46;"U$24";"SMA2";1;"";;;
47;"PWR0,PPS_LED0";"SMT-JUMPER_2_NC_TRACE_SILK";2;"JUMPER-SMT_2_NC_TRACE_SILK";;;
48;"U$16";"#TX#0";1;"";;;
49;"U$36";"#PWR#0";1;"";;;
50;"U$13";"##SAFE##0";1;"";;;
51;"U$46";"#EINT_#0";1;"";;;
52;"U$32";"#SCL#1";1;"";;;
53;"U$30";"#I�C#0";1;"";;;
54;"U$33";"#SDA#0";1;"";;;
55;"JP5";"SMT-JUMPER_3_NO_SILK";1;"JUMPER-SMT_3_NO_SILK";;;
56;"U$15";"#RX#1";1;"";;;
57;"LOGO2";"SFE_LOGO_NAME_FLAME_.1";1;"SFE_LOGO_NAME_FLAME.1_INCH";;;
58;"U$12";"##RST##2";1;"";;;
59;"MEAS0";"COMBO-JUMPER_2_NC_TRACE";1;"JUMPER-COMBO_2_NC_TRACE";;;

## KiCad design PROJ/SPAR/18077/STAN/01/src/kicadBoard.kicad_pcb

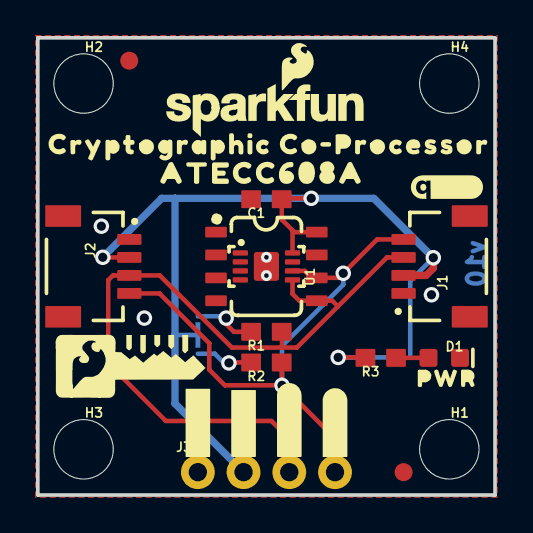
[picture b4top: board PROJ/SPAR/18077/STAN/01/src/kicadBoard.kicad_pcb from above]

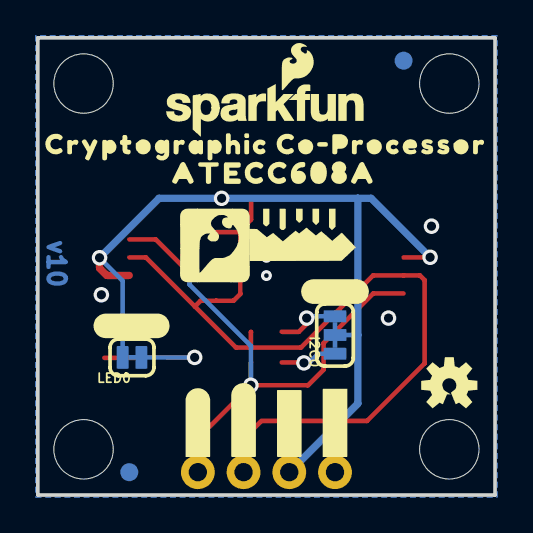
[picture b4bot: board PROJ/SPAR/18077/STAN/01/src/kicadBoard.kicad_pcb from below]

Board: 2 copper layers, 25.4 x 25.4 mm, 41 parts (15 on the bottom side), 8 nets.

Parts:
C1: 0.1uF; 0603
D1: RED; LED-0603
FD1, FD2, FD3, FD4: FIDUCIAL1X2; FIDUCIAL-1X2
FRAME1: FRAME-LETTER; CREATIVE_COMMONS
H1, H2, H3, H4: STAND-OFF
I2C0: SMT-JUMPER_3_2-NC_TRACE_SILK
J1, J2: QWIIC; JST04_1MM_RA
J3: PTH; 1X04_NO_SILK
LED0: SMT-JUMPER_2_NC_TRACE_SILK
LOGO1, LOGO2: SFE_LOGO_NAME_FLAME.1_INCH; SFE_LOGO_NAME_FLAME_.1
LOGO3: QWIIC_LOGO_4MM; QWIIC_4MM
LOGO4: OSHW-LOGOS; OSHW-LOGO-S
R1, R2: 4.7k; 0603
R3: 1k; 0603
U1: ATECC608A; DUAL_UDFN_2X3MM_SOIC-8
U$1: #I2C#0
U$2, U$13: #SCL#0
U$3: #LED#0
U$4, U$17: #SDA#0
U$5, U$7: ATECC608A0
U$6, U$20: #3V3#0
U$8: CRYPTO_COPROCESSOR_LOGO_LARGE
U$9, U$19: CRYPTOGRAPHIC_CO#PROCESSOR0
U$10: CRYPTO_COPROCESSOR_LOGO_SMALL
U$11: PWR0
U$21, U$23: #GND#0

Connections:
3.3V: C1.1, I2C0.2, J1.2, J2.2, J3.2, LED0.2, U1.8, U1.8S
GND: C1.2, D1.C, J1.1, J2.1, J3.1, U1.4, U1.4S, U1.P
unnamed: D1.A, R3.1
unnamed: I2C0.3, R1.2
unnamed: I2C0.1, R2.2
unnamed: LED0.1, R3.2
SCL: J1.4, J2.4, J3.4, R2.1, U1.6, U1.6S
SDA: J1.3, J2.3, J3.3, R1.1, U1.5, U1.5S

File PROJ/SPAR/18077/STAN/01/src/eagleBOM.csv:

"Part";"Value";"Device";"Package";"Description";"DESIGNER";"PROD_ID";"REV";"VALUE";
"C1";"0.1uF";"0.1UF-0603-25V-(+80/-20%)";"0603";"0.1µF ceramic capacitors";"";"CAP-00810";"";"0.1uF";
"D1";"RED";"LED-RED0603";"LED-0603";"Red SMD LED";"";"DIO-00819";"";"RED";
"FD1";"FIDUCIAL1X2";"FIDUCIAL1X2";"FIDUCIAL-1X2";"Fiducial Alignment Points";"";"";"";"";
"FD2";"FIDUCIAL1X2";"FIDUCIAL1X2";"FIDUCIAL-1X2";"Fiducial Alignment Points";"";"";"";"";
"FD3";"FIDUCIAL1X2";"FIDUCIAL1X2";"FIDUCIAL-1X2";"Fiducial Alignment Points";"";"";"";"";
"FD4";"FIDUCIAL1X2";"FIDUCIAL1X2";"FIDUCIAL-1X2";"Fiducial Alignment Points";"";"";"";"";
"FRAME1";"FRAME-LETTER";"FRAME-LETTER";"CREATIVE_COMMONS";"Schematic Frame - Letter";"";"";"";"";
"H1";"STAND-OFF";"STAND-OFF";"STAND-OFF";"Stand Off";"";"";"";"";
"H2";"STAND-OFF";"STAND-OFF";"STAND-OFF";"Stand Off";"";"";"";"";
"H3";"STAND-OFF";"STAND-OFF";"STAND-OFF";"Stand Off";"";"";"";"";
"H4";"STAND-OFF";"STAND-OFF";"STAND-OFF";"Stand Off";"";"";"";"";
"I2C";"";"JUMPER-SMT_3_2-NC_TRACE_SILK";"SMT-JUMPER_3_2-NC_TRACE_SILK";"Normally closed trace jumper (2 of 2 connections)";"";"";"";"";
"J1";"QWIIC";"I2C_STANDARDQWIIC";"JST04_1MM_RA";"SparkFun I2C Standard Pinout Header";"";"CONN-13694";"";"Qwiic Right Angle";
"J2";"QWIIC";"I2C_STANDARDQWIIC";"JST04_1MM_RA";"SparkFun I2C Standard Pinout Header";"";"CONN-13694";"";"Qwiic Right Angle";
"J3";"PTH";"I2C_STANDARD_NO_SILK";"1X04_NO_SILK";"SparkFun I2C Standard Pinout Header";"";"";"";"";
"LED";"";"JUMPER-SMT_2_NC_TRACE_SILK";"SMT-JUMPER_2_NC_TRACE_SILK";"Normally closed trace jumper";"";"";"";"";
"LOGO1";"SFE_LOGO_NAME_FLAME.1_INCH";"SFE_LOGO_NAME_FLAME.1_INCH";"SFE_LOGO_NAME_FLAME_.1";"SparkFun Font Logo w/ Flame";"";"";"";"";
"LOGO3";"QWIIC_LOGO_4MM";"QWIIC_LOGO_4MM";"QWIIC_4MM";"Qwiic Logos for placement on schematic and PCB. The 5.5mm silk logo is best for placing next to Qwiic connector.";"";"";"";"";
"LOGO4";"OSHW-LOGOS";"OSHW-LOGOS";"OSHW-LOGO-S";"Open-Source Hardware (OSHW) Logo";"";"";"";"";
"R1";"4.7k";"4.7KOHM-0603-1/10W-1%";"0603";"4.7kΩ resistor";"";"RES-07857";"";"4.7k";
"R2";"4.7k";"4.7KOHM-0603-1/10W-1%";"0603";"4.7kΩ resistor";"";"RES-07857";"";"4.7k";
"R3";"1k";"1KOHM-0603-1/10W-1%";"0603";"1kΩ resistor";"";"RES-07856";"";"1k";
"U1";"ATECC608A";"ATECC608ADUAL_PACKAGE_UDFN_SOIC-8";"DUAL_UDFN_2X3MM_SOIC-8";"ATECC608A CryptoAuthentication Device";"";"IC-15951";"";"";

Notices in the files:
parts and their libraries:
RELEASED UNDER THE CREATIVE COMMONS ATTRIBUTION SHARE-ALIKE 4.0 LICENSE
HTTPS://CREATIVECOMMONS.ORG/LICENSES/BY-SA/4.0
